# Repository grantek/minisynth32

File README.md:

# Minisynth 32

A 3D-printable MIDI synthesiser inspired by the Roland MT-32 and
[clumsyMIDI](https://github.com/gmcn42/clumsyMIDI), and powered by the
[mt32-pi](https://github.com/dwhinham/mt32-pi/wiki) MT-32 emulator.

## Features

* 3D printable shell, 50% scale of the original MT-32
* GY-PCM5102 HiFi DAC board
* Front panel PCB with 2-10 tactile switches and 0.91" OLED Display
* Optional 2- or 10-button clickable front panel (only 2 buttons are functional)
* Rear I/O breakout PCB with 5.5mm power jack and pushbutton power switch
* Rotary encoder volume dial (generic 12mm shaft with no carrier board)
* MIDI Input via DIN5 MIDI cable or USB (using additional Arduino board)
* Completely through-hole soldering, no surface mount components
* Works with the Raspberry Pi "A" or "B" variants

## Warnings

**NO WARRANTY is provided, and no guarantee that all or any of the parts will
fit together. 3D printing is time-consuming and an art at the best of times.**

However, if you're stuck or have a question, feel free to open an issue on
GitHub, and the worst you'll get is sympathy.

## Assembly Notes

Check the [Bill of Materials](minisynth32-bom.csv) for all of the parts needed,
and the [project wiki](https://github.com/grantek/minisynth32/wiki) for the
build guide with pictures, a [text-only copy](build-guide.md) is included in
this repository.

## News

This is "Version 2.0" of the Minisynth 32, the previous version had a simpler
faceplate with 2 large, easy to print buttons. If you're looking for the old
version, see the "ms32-v1.0" tag/release.

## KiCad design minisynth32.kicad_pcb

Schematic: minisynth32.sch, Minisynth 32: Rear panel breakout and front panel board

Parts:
A1: GY-PCM5102
C1: 470u 10V; CP_Radial_D8.0mm_P3.50mm
C2, C4: 100n; C_Rect_L7.0mm_W2.0mm_P5.00mm
C3: 100u; CP_Radial_D6.3mm_P2.50mm
D1: 1N4148; D_DO-35_SOD27_P7.62mm_Horizontal
J1: F_PANEL; PinHeader_1x06_P2.54mm_Vertical
J2: Conn_02x20_Odd_Even; PinSocket_2x20_P2.54mm_Vertical
J3: PJ-002A; CUI_PJ-002A
J4: ROT_HDR; PinHeader_1x04_P2.54mm_Vertical
J5: MIDI_IN; PinHeader_1x02_P2.54mm_Vertical
J6: R_BREAKOUT; PinHeader_1x06_P2.54mm_Vertical
J7: SSD1306 OLED; SSD1306_128_32
J8: UNUSED_2; PinHeader_1x04_P2.54mm_Vertical
J9: UNUSED_1; PinHeader_1x04_P2.54mm_Vertical
R1: 1k; R_Axial_DIN0207_L6.3mm_D2.5mm_P10.16mm_Horizontal
R2: 220R; R_Axial_DIN0207_L6.3mm_D2.5mm_P10.16mm_Horizontal
SW1: B1; TL59N
SW2: B2; TL59N
SW3, SW4, SW5, SW6, SW7, SW8, SW9, SW10: SW_Push; TL59N
SW11: PB400EEQR1BLK
U1: H11L1; DIP-6_W7.62mm

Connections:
+3V3: C2.1, J2.1, R1.2, U1.6
+5V: A1.6 (VIN), C1.1, C3.1, C4.1, J1.4, J2.2, J2.4, SW11.2
/GPIO5: J2.29
/GPIO6: J2.31
/GPIO7(SPI1_CE_N): J2.26
/GPIO8(SPI0_CE_N): J2.24
/GPIO9(SPI0_MISO): J2.21
/GPIO10(SPI0_MOSI): J2.19
/GPIO11(SPI0_CLK): J2.23
/GPIO12(PWM0): J2.32
/GPIO13(PWM1): J2.33
/GPIO14(TXD0): J2.8
/GPIO15(RXD0): J2.10, R1.1, U1.4
/GPIO16: J2.36
/GPIO20(SPI1_MOSI): J2.38
/GPIO24(GEN5): J2.18
/GPIO25(GEN6): J2.22
/GPIO26: J2.37
/ID_SC: J2.28
/ID_SD: J2.27
BTN1: J1.2, J2.11
BTN2: J1.1, J2.13
ENC_BTN: J2.7, J4.2
ENC_CLK: J2.15, J4.3
ENC_DAT: J2.16, J4.4
GND: A1.1 (SCK), A1.5 (GND), C1.2, C2.2, C3.2, C4.2, J1.3, J2.6, J2.9, J2.14, J2.20, J2.25, J2.30, J2.34, J2.39, J3.2, J4.1, U1.5
GND2: J6.3, J7.1, SW1.2, SW2.2, SW3.2, SW4.2, SW5.2, SW6.2, SW7.2, SW8.2, SW9.2, SW10.2
I2C_SCL: J1.5, J2.5
I2C_SDA: J1.6, J2.3
I2S_BCLK: A1.2 (BCK), J2.12
I2S_DATA: A1.3 (DIN), J2.40
I2S_LRCLK: A1.4 (LCK), J2.35
unnamed: D1.1 (K), R2.2, U1.1
unnamed: D1.2 (A), J5.1, U1.2
unnamed: J3.1, SW11.1
unnamed: J5.2, R2.1
unnamed: J6.1, SW1.1
unnamed: J6.2, SW2.1
unnamed: J6.4, J7.2
unnamed: J6.5, J7.3
unnamed: J6.6, J7.4
unnamed: J8.1, SW8.1
unnamed: J8.2, SW9.1
unnamed: J8.3, SW10.1
unnamed: J8.4, SW4.1
unnamed: J9.1, SW5.1
unnamed: J9.2, SW6.1
unnamed: J9.3, SW7.1
unnamed: J9.4, SW3.1

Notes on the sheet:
To MIDI jack pin 4
To MIDI jack pin 5
Rotary encoder (12mm shaft) is wired directly to ROT_HDR
Front Panel PCB
UNUSED Front Panel buttons These may connect to a future version of mt32-pi, or tactile switches may be placed that have no connection

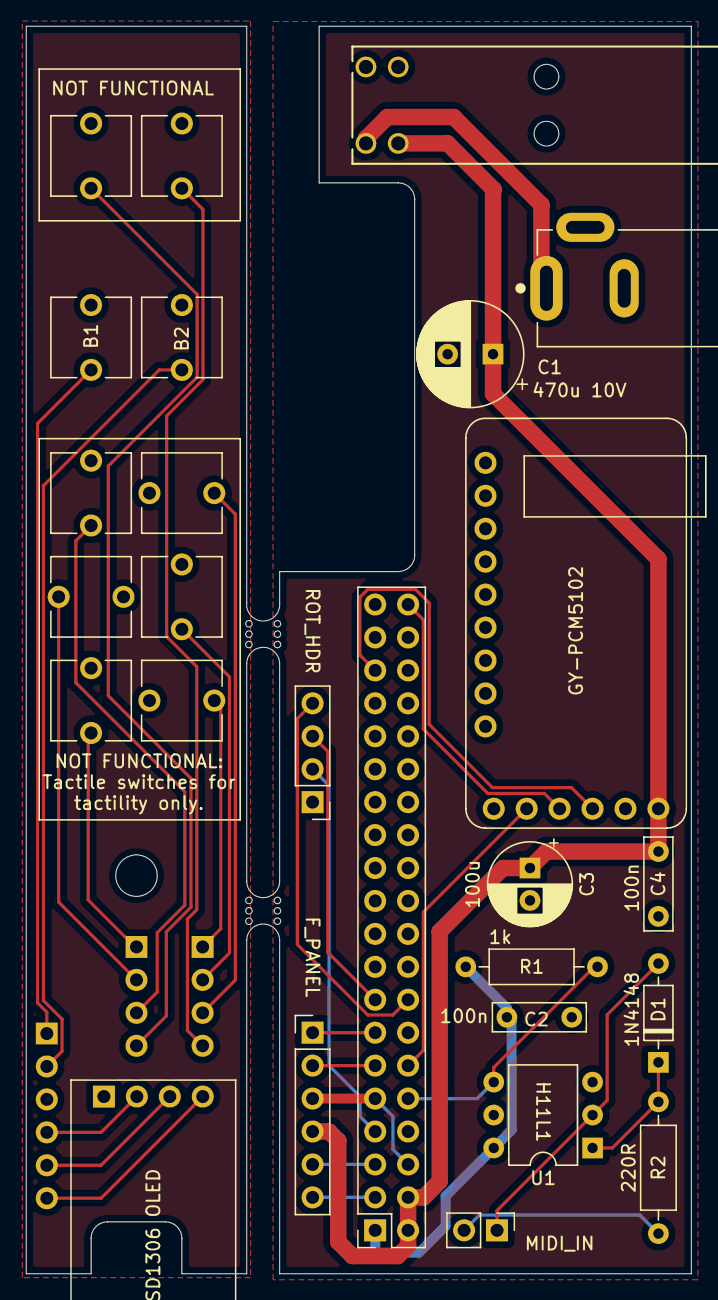
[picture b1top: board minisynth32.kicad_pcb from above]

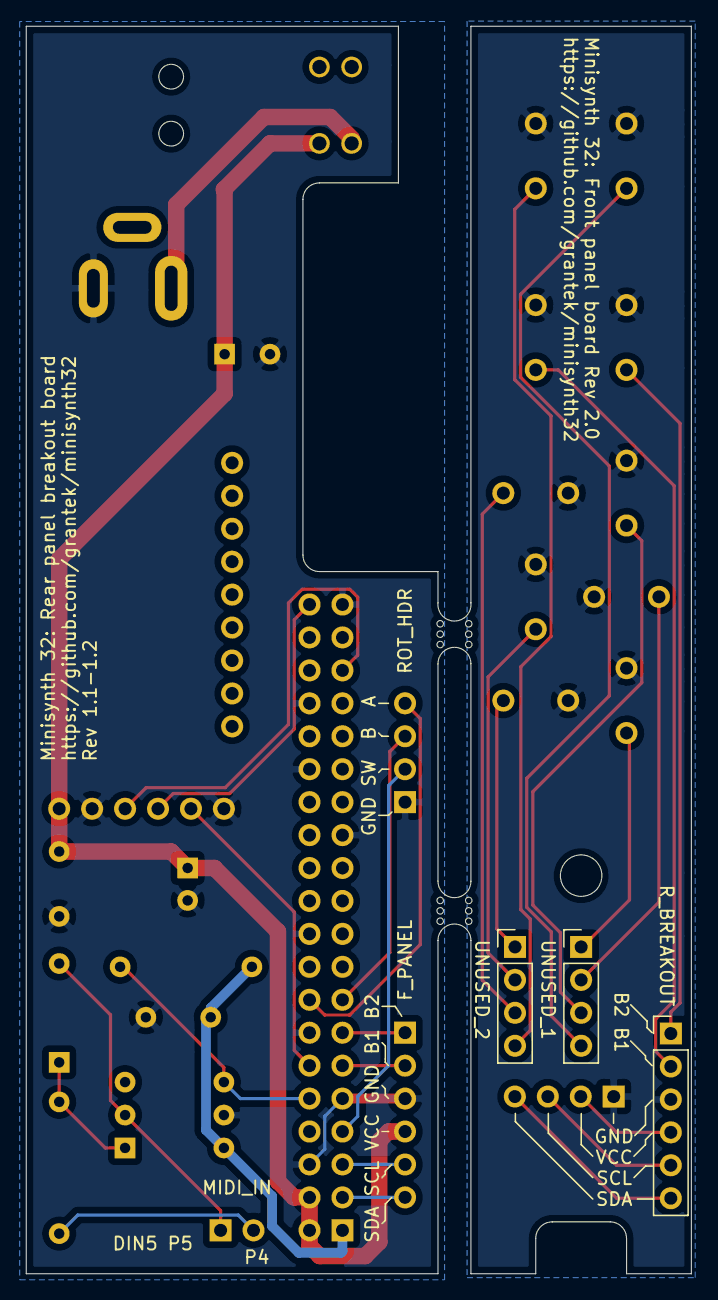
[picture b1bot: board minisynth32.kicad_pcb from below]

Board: 2 copper layers, 51.3 x 96.2 mm, 31 parts (3 on the bottom side), 32 nets.

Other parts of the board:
mouse-bite-2.54mm-slot, mouse-bite-2.54mm-slot#2: VAL**; mouse-bite-2.54mm-slot

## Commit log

2021-05-07 Initial commit: Rear/Front PCB v1.0
2021-05-08 Move ROT_HDR for RPi 3B
2021-05-10 Add separate PCB files, gerbers, readme, license, bom
2021-05-11 Add 3D models
2021-05-11 Update shell, README
    face:
    - add clearance to edges and bolt mounts
    - add hex nut pockets to bolt mounts
    - add face lines to imitate MT-32 display plate
    face, base, top:
    - new mating lips with more clearance
2021-05-13 PCB rev 1.1 (rear only): cutaway to support RPi3B
2021-05-15 Rev 1.1 F/R PCBs, tuned base and top
2021-05-17 Minor 3D updates and documentation
2021-05-18 Minor updates to face
    - standardise cuts for the threaded inserts
    - add hard support for knobwall
2021-05-22 Add quick photo for README
2021-05-30 Change Pi mounting to M2.5 bolts
    Updated BOM/README/CHANGELOG to suit.
    Also properly rotated face "knobwall" hard support so it doesn't interfere with the backplate.
2021-07-08 Documentation updates
2021-08-01 WIP face v2
2021-08-01 Add rebackplate.FCstd (only had STL there)
2021-08-17 face v2
2021-08-25 front pcb v2
2021-08-26 doco and stuff
2021-09-01 10-button updates
2021-09-06 arduino pro micro variant of base
2021-09-07 add MIDIUARTUSB, clean up models, update BOM
2021-09-28 remove oled clearance as it was causing artifacts in the front face
2021-09-28 add news of 10but branch to README.md
2021-09-28 move text-only build guide to separate file
2021-10-02 updates to 3d models
    face:
    - redo bottom lip to suit base tabs
    - rework clearance cuts
    base:
    - tune reclearancefill
    - work on usb apm mount
2021-10-06 Update models
    - fix base wall mirroring (was incorrectly rotated before)
    - rework MCU base to fit different types of MCU board
    - add parametric (via spreadsheet) MCU clamp
    - remove 2mm shim STL as testing showed it too thick for thin OLED board
2021-10-06 render face-2but and create separate tree in FCStd
2021-10-07 Silkscreen update to front and F/R PCBs
    Updated Silkscreen text for extra buttons to read "NOT FUNCTIONAL" instead of "UNUSED", and got rid of the cross through them to avoid confusion.
2021-10-07 Update BOM and README
    Also re-add 2mm shim
2021-10-07 Lower MCU default boardheight to 5mm
2021-10-07 Split build guide into separate file
2021-10-08 lengthen lip on top shell
2021-10-08 update photo for README
2021-10-08 Minor updates to build guide
2021-10-08 minor documentation fixes
2021-10-08 Minor proposal (line 03)
2021-10-08 Minor proposal (line 115)
2021-10-09 minor fixes to BOM
2022-06-04 Minor documentation update
    - Slightly better photo to replace the crappy phone pic.
    - Sync wiki to build guide (and revert to British spelling).

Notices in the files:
minisynth32.kicad_pcb:
(c) 2021 Grant King CC-BY-SA-4.0
